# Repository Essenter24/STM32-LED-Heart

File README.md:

# STM32 LED Heart

An STM32-based embedded project that drives a heart-shaped LED array,
implementing custom LED control and timing logic to create animated
lighting effects.

## Features
- Heart-shaped LED arrangement
- STM32-based LED control
- Custom lighting animations

## Hardware
- Microcontroller: STM32G030K8T6
- LEDs: 16 red LEDs

## Project Status
Completed

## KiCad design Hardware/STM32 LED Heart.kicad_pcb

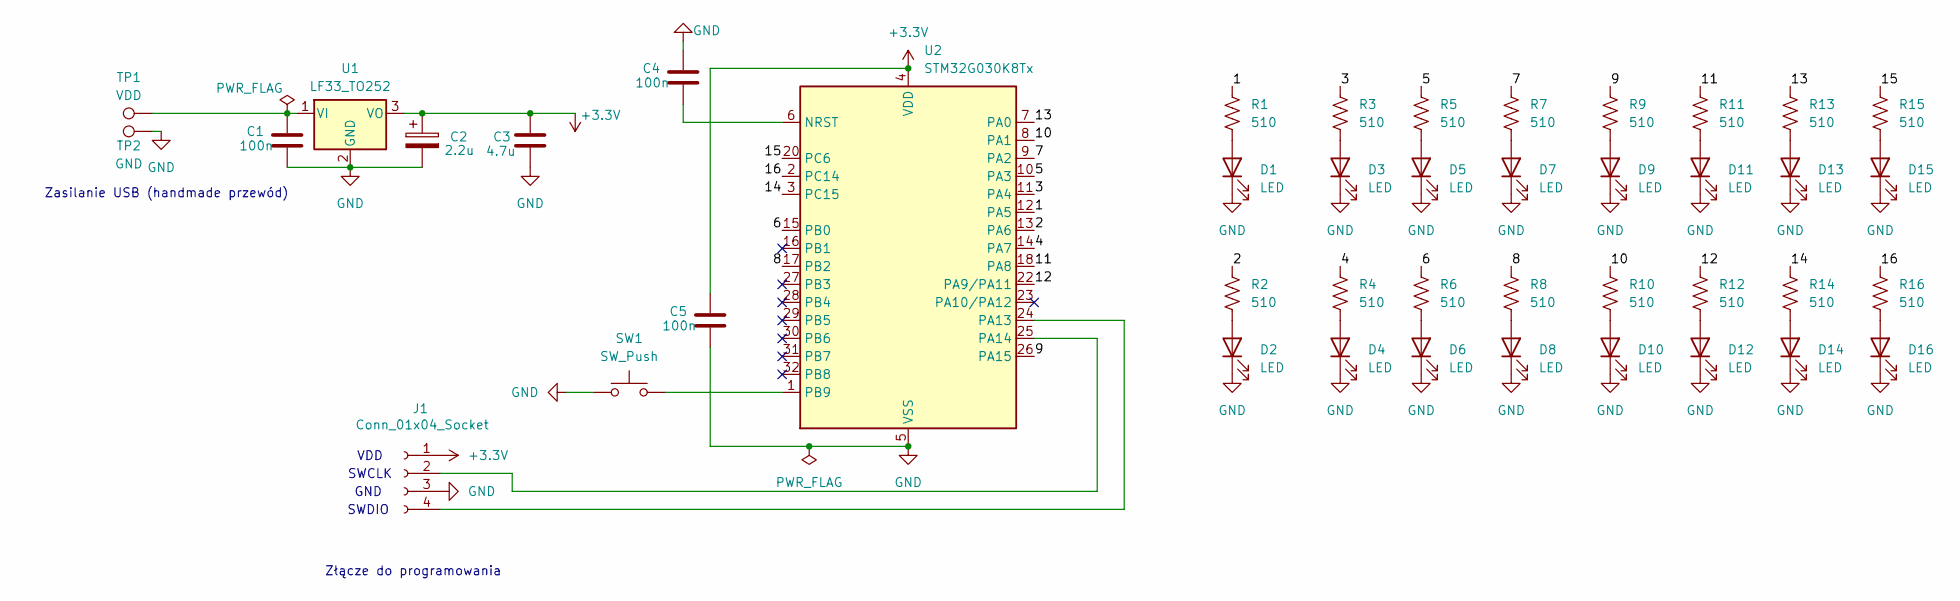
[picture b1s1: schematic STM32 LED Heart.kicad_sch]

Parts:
C1, C4, C5: 100n; C_0603_1608Metric
C2: 2.2u; CP_Elec_4x5.3
C3: 4.7u; C_0603_1608Metric
D1, D2, D3, D4, D5, D6, D7, D8, D9, D10, D11, D12, D13, D14, D15, D16: LED; LED_D5.0mm
J1: Conn_01x04_Socket; PinHeader_1x04_P2.54mm_Vertical_SMD_Pin1Left
R1, R2, R3, R4, R5, R6, R7, R8, R9, R10, R11, R12, R13, R14, R15, R16: 510; R_0603_1608Metric
SW1: SW_Push; SW_Tactile_SPST_Angled_PTS645Vx58-2LFS
TP1: VDD; TestPoint_Pad_2.5x2.5mm
TP2: GND; TestPoint_Pad_2.5x2.5mm
U1: LF33_TO252; TO-252-2
U2: STM32G030K8Tx; LQFP-32_7x7mm_P0.8mm

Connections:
+3.3V: C2.1, C3.1, C5.1, J1.1, U1.3 (VO), U2.4 (VDD)
/1: R1.1, U2.12 (PA5)
/2: R2.1, U2.13 (PA6)
/3: R3.1, U2.11 (PA4)
/4: R4.1, U2.14 (PA7)
/5: R5.1, U2.10 (PA3)
/6: R6.1, U2.15 (PB0)
/7: R7.1, U2.9 (PA2)
/8: R8.1, U2.17 (PB2)
/9: R9.1, U2.26 (PA15)
/10: R10.1, U2.8 (PA1)
/11: R11.1, U2.18 (PA8)
/12: R12.1, U2.22 (PA9/PA11)
/13: R13.1, U2.7 (PA0)
/14: R14.1, U2.3 (PC15)
/15: R15.1, U2.20 (PC6)
/16: R16.1, U2.2 (PC14)
GND: C1.2, C2.2, C3.2, C4.1, C5.2, D1.1 (K), D2.1 (K), D3.1 (K), D4.1 (K), D5.1 (K), D6.1 (K), D7.1 (K), D8.1 (K), D9.1 (K), D10.1 (K), D11.1 (K), D12.1 (K), D13.1 (K), D14.1 (K), D15.1 (K), D16.1 (K), J1.3, SW1.1, TP2.1 (1_1), U1.2 (GND), U2.5 (VSS)
unnamed: D1.2 (A), R1.2
unnamed: D2.2 (A), R2.2
unnamed: D3.2 (A), R3.2
unnamed: D4.2 (A), R4.2
unnamed: D5.2 (A), R5.2
unnamed: D6.2 (A), R6.2
unnamed: D7.2 (A), R7.2
unnamed: D8.2 (A), R8.2
unnamed: D9.2 (A), R9.2
unnamed: D10.2 (A), R10.2
unnamed: D11.2 (A), R11.2
unnamed: D12.2 (A), R12.2
unnamed: D13.2 (A), R13.2
unnamed: D14.2 (A), R14.2
unnamed: D15.2 (A), R15.2
unnamed: D16.2 (A), R16.2
unnamed: J1.2, U2.25 (PA14)
unnamed: J1.4, U2.24 (PA13)
unnamed: C1.1, TP1.1 (1_1), U1.1 (VI)
unnamed: C4.2, U2.6 (NRST)
unnamed: SW1.2, U2.1 (PB9)

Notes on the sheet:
SWDIO
Zasilanie USB (handmade przewód)
VDD
SWCLK
GND
Złącze do programowania

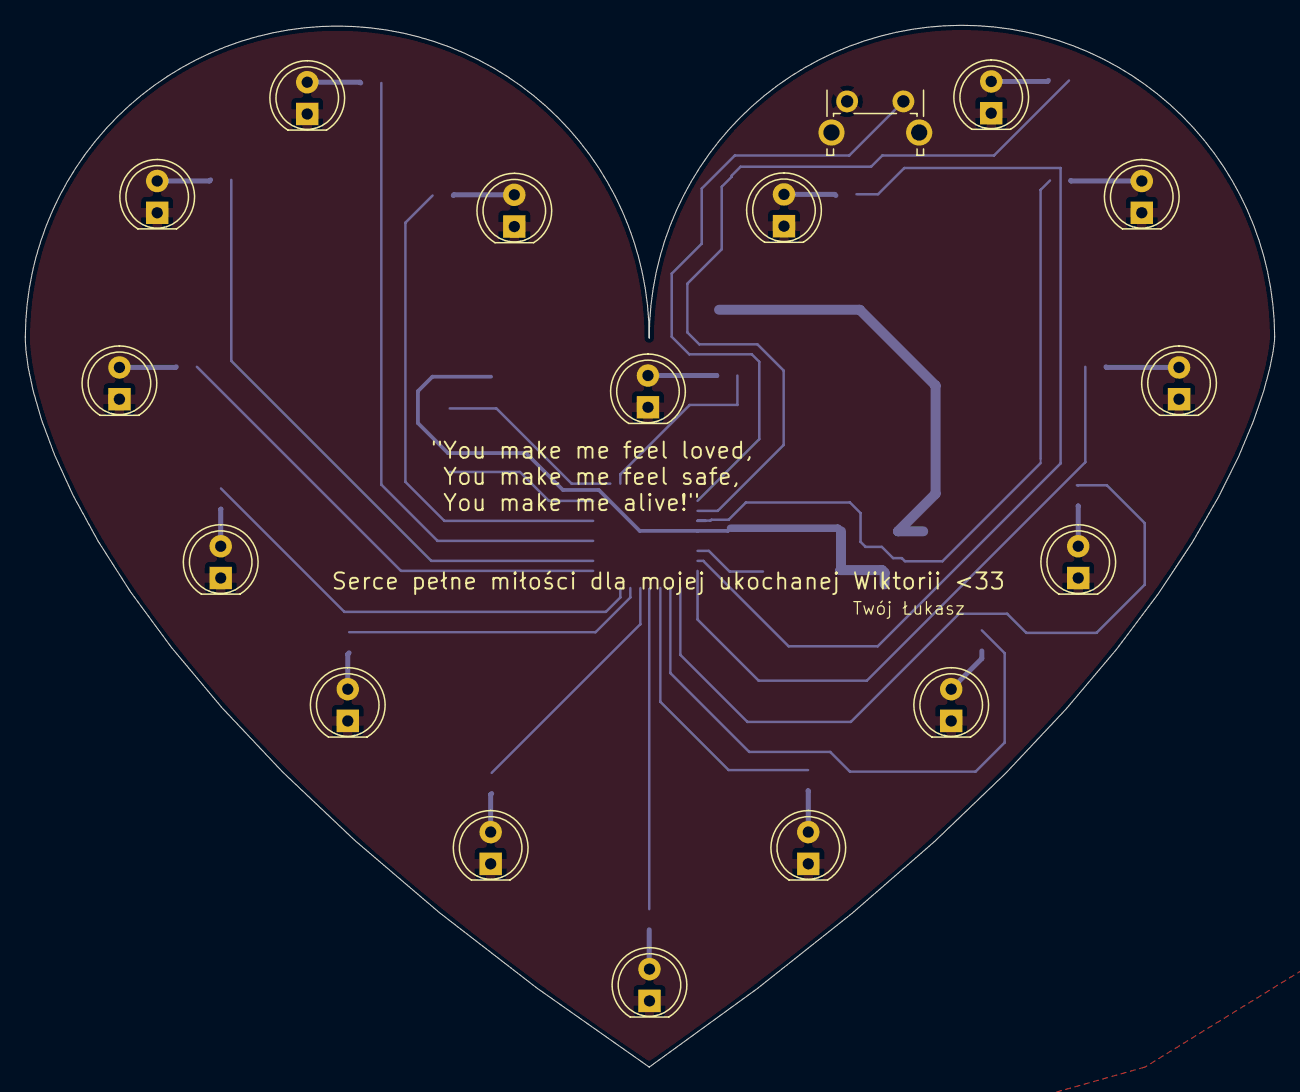
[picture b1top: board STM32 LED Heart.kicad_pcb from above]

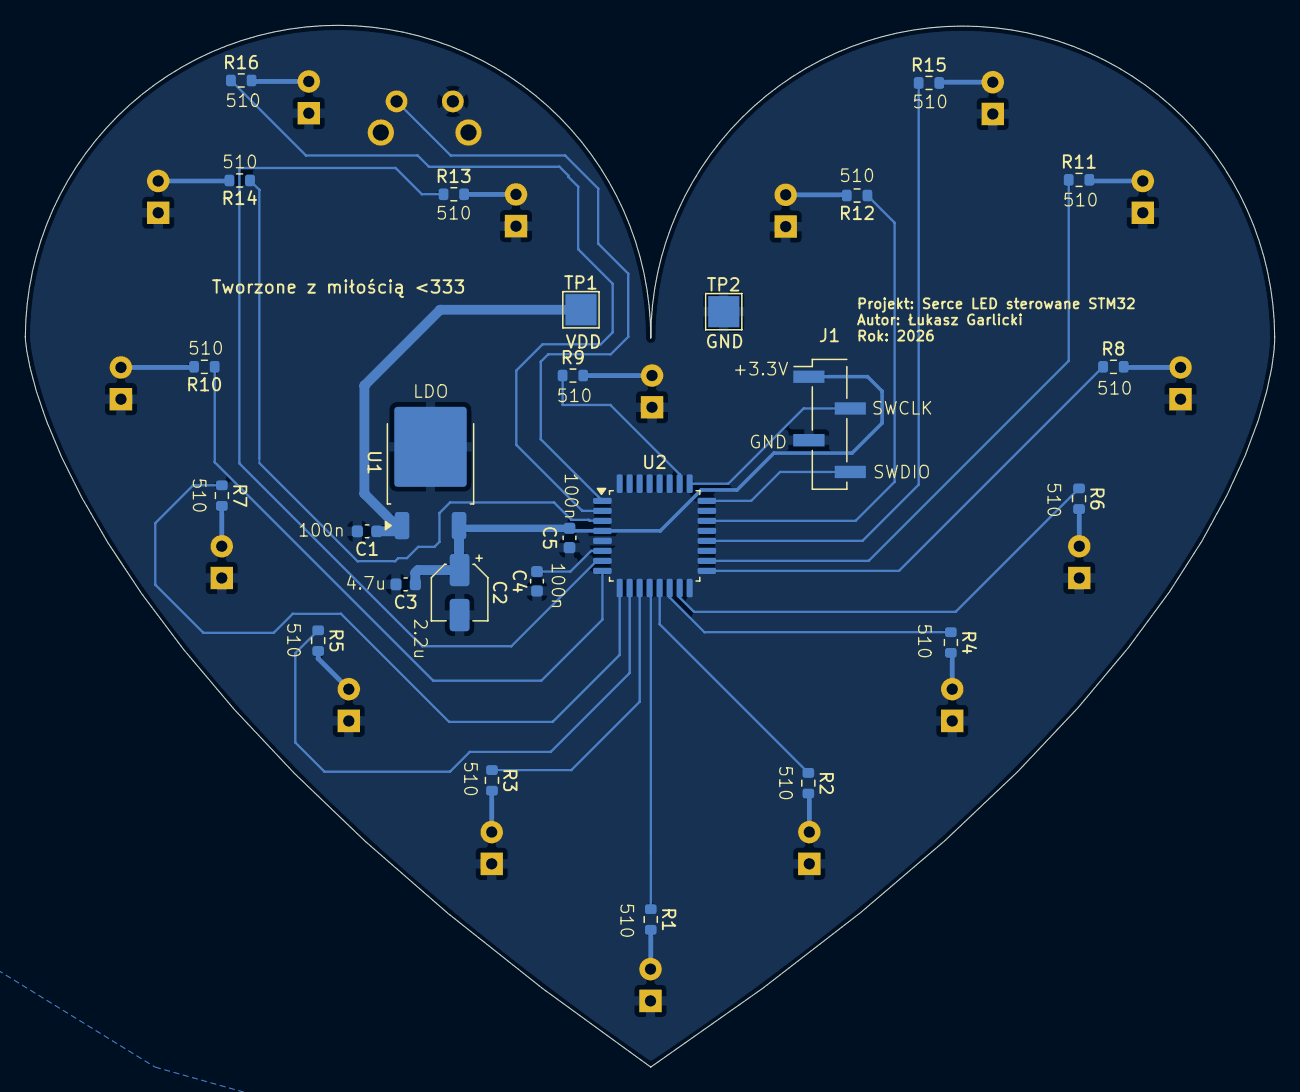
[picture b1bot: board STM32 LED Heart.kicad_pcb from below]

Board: 2 copper layers, 99.9 x 83.3 mm, 43 parts (26 on the bottom side), 39 nets.

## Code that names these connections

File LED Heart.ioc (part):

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Mcu.Name=STM32G030K(6-8)Tx
Mcu.Package=LQFP32
Mcu.UserName=STM32G030K8Tx
PA0.GPIOParameters=GPIO_Label
PA0.GPIO_Label=D13
PA0.Signal=GPIO_Output
PA1.GPIOParameters=GPIO_Label
PA1.GPIO_Label=D10
PA1.Signal=GPIO_Output
PA11\ [PA9].GPIOParameters=GPIO_Label
PA11\ [PA9].GPIO_Label=D12
PA11\ [PA9].Signal=GPIO_Output
PA15.GPIOParameters=GPIO_Label
PA15.GPIO_Label=D9
PA15.Signal=GPIO_Output
PA2.GPIOParameters=GPIO_Label
PA2.GPIO_Label=D7
PA2.Signal=GPIO_Output
PA3.GPIOParameters=GPIO_Label
PA3.GPIO_Label=D5
PA3.Signal=GPIO_Output
PA4.GPIOParameters=GPIO_Label
PA4.GPIO_Label=D3
PA4.Signal=GPIO_Output
PA5.GPIOParameters=GPIO_Label
PA5.GPIO_Label=D1
PA5.Signal=GPIO_Output
PA6.GPIOParameters=GPIO_Label
PA6.GPIO_Label=D2
PA6.Signal=GPIO_Output
PA7.GPIOParameters=GPIO_Label
PA7.GPIO_Label=D4
PA7.Signal=GPIO_Output
PA8.GPIOParameters=GPIO_Label
PA8.GPIO_Label=D11
PA8.Signal=GPIO_Output
PB0.GPIOParameters=GPIO_Label
PB0.GPIO_Label=D6
PB0.Signal=GPIO_Output
PB2.GPIOParameters=GPIO_Label
PB2.GPIO_Label=D8
PB2.Signal=GPIO_Output
PB9.GPIOParameters=GPIO_PuPd,GPIO_Label,GPIO_ModeDefaultEXTI
PB9.GPIO_Label=BUTTON
PB9.GPIO_ModeDefaultEXTI=GPIO_MODE_IT_FALLING
PB9.GPIO_PuPd=GPIO_PULLUP
PB9.Signal=GPXTI9
PC14-OSC32_IN\ (PC14).GPIOParameters=GPIO_Label
PC14-OSC32_IN\ (PC14).GPIO_Label=D16
PC14-OSC32_IN\ (PC14).Signal=GPIO_Output
PC15-OSC32_OUT\ (PC15).GPIOParameters=GPIO_Label
PC15-OSC32_OUT\ (PC15).GPIO_Label=D14
PC15-OSC32_OUT\ (PC15).Signal=GPIO_Output
PC6.GPIOParameters=GPIO_Label
PC6.GPIO_Label=D15
PC6.Signal=GPIO_Output
RCC.HSE_VALUE=8000000
RCC.SYSCLKFreq_VALUE=16000000
board=custom
